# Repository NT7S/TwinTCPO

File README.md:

# Twin-T Code Practice Oscillator (Amogus Edition)

A battery-powered code practice oscillator for amateur radio operators. The
board is a two-layer, through-hole design built around a twin-T audio
oscillator feeding a pair of NE5532 buffers. The "Amogus" edition is a
novelty layout shaped and silkscreened as a crewmate.

## Overview

The oscillator core is a discrete common-emitter stage (Q2, 2N4401) with a
twin-T notch network in its feedback path. A MOSFET (Q1) buffers the key
input and drives a second MOSFET (Q3) that modulates the notch, giving a
clean keying envelope with a minimum of clicks. Two LEDs provide power and
key-down indication. The audio output is buffered by both halves of an
NE5532 and fed to a 1/8" headphone jack.

## Specifications

| Parameter | Value |
|-----------|-------|
| Supply | 9 V battery (6F22 / PP3) |
| Supply current | ~2 mA quiescent |
| Oscillator frequency | ~480 Hz nominal (1/(2πRC), R = 3.3 kΩ, C = 100 nF); verify by measurement |
| Output | 1/8" (3.5 mm) headphone jack, AC-coupled |
| Board size | 120.6 × 120.0 mm, 2-layer, 1.6 mm FR4 |
| Keying | MOSFET-switched twin-T notch; no audible clicks in normal use |

## Repository contents

| Path | Description |
|------|-------------|
| `pcb/` | KiCad project (schematic, board, Gerbers, drill) |
| `pcb/TwinTCPO.kicad_pcb` | KiCad board file (rev A as built, 2021) |
| `pcb/TwinTCPO.kicad_sch` | KiCad schematic (re-saved 2023, see rev notes) |
| `pcb/TwinTCPO*.gbr`, `pcb/TwinTCPO.drl` | Committed fabrication outputs (2021) |
| `BOM.csv` | Bill of materials, generated from the board's as-built values |
| `docs/REV-A-NOTES.md` | As-built revision notes and known discrepancies |
| `media/` | Artwork and mechanical assets (SVG, PDF, TIF, XCF) |

## Build notes

1. Use `BOM.csv` for parts; it reflects the **board as fabricated** (rev A,
   2021), not the current schematic. The `Notes` column flags every reference
   whose schematic value differs.
2. Read `docs/REV-A-NOTES.md` before ordering parts. In particular, **C11 is
   1 µF on the board but 100 µF in the schematic, and the schematic is the
   correct value** — at 32 Ω the as-built 1 µF rolls off from ~5 kHz and costs
   about 20 dB at the 480 Hz tone. Use 100 µF (or 47 µF) unless you specifically
   intend high-impedance headphones. **R6 is the opposite case: the board's
   3.3 kΩ is correct and the schematic's 330 Ω is the error.**
3. The committed Gerbers and drill file regenerate exactly from
   `TwinTCPO.kicad_pcb`; they are safe to send to a fabricator as-is.
4. The board has no mounting holes. Confirm your enclosure retains it.

## License

This design is licensed under the Creative Commons Attribution-ShareAlike 4.0
International License. See `LICENSE` for the full text. You are free to share
and adapt the design, provided you credit the original author and distribute
derivatives under the same terms.

## Links

- [Etherkit](https://www.etherkit.com)
- [NT7S / Jason Milldrum](https://nt7s.com)

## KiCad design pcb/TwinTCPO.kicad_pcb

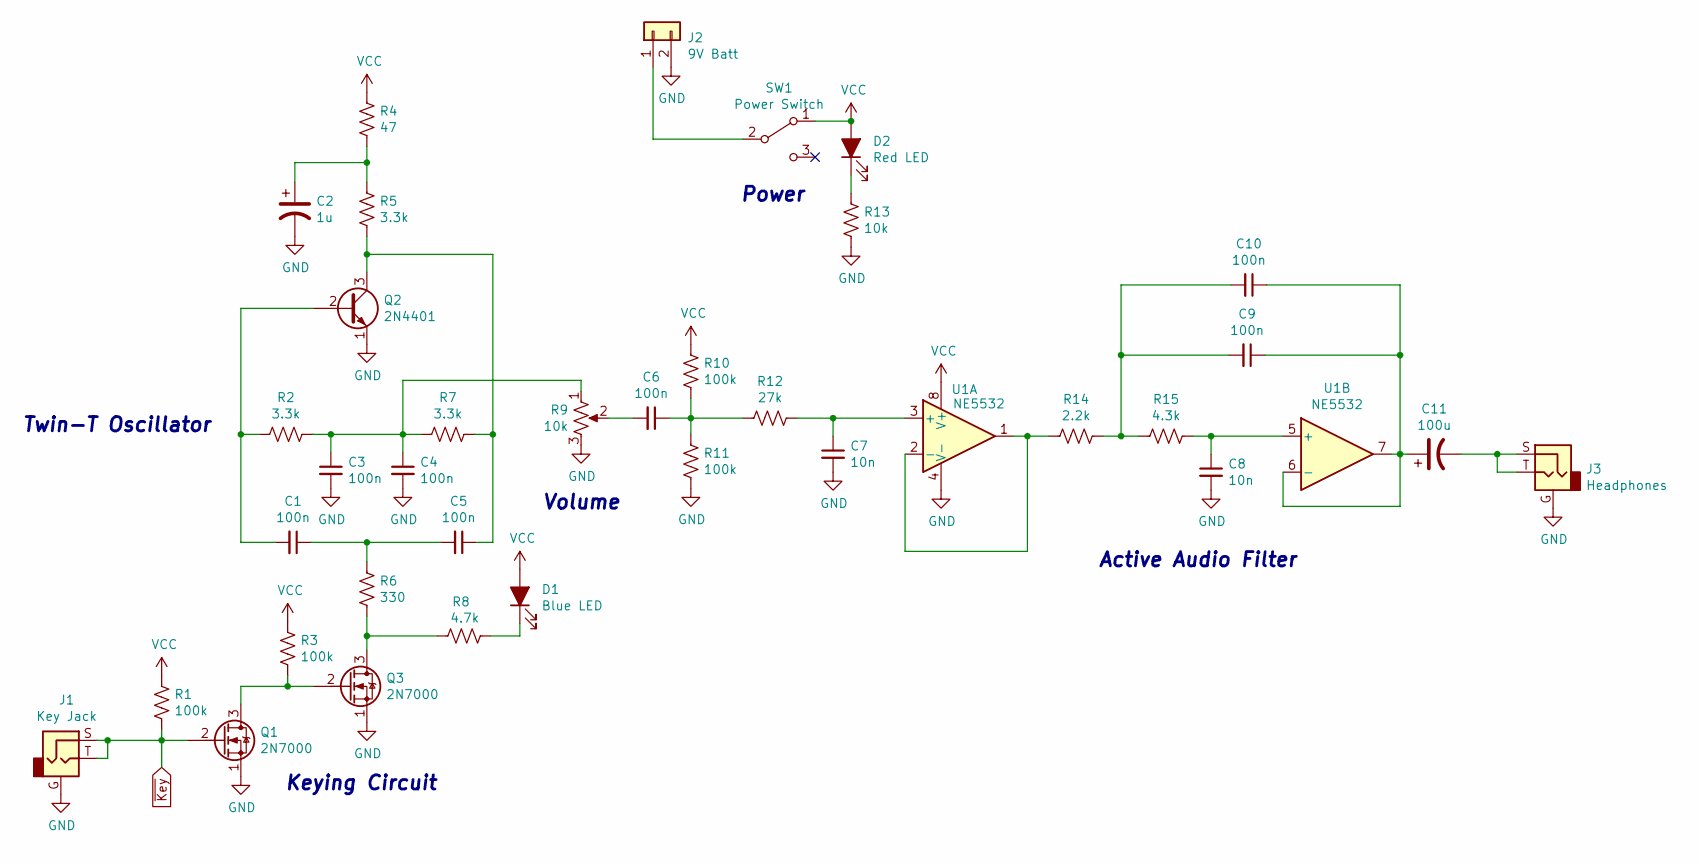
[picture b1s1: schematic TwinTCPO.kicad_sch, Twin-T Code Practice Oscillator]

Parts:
C1, C3, C4, C5, C6, C9, C10: 100n; C_Disc_D4.3mm_W1.9mm_P5.00mm
C2: 1u; CP_Radial_D5.0mm_P2.00mm
C7, C8: 10n; C_Disc_D4.3mm_W1.9mm_P5.00mm
C11: 100u; CP_Radial_D5.0mm_P2.00mm
D1: Blue LED; Kingbright_AA3528QBS_D09
D2: Red LED; LED_D5.0mm
J1: Key Jack; Kycon_STX-3120-3B
J2: 9V Batt; Eagle_12BH611-GR
J3: Headphones; Kycon_STX-3120-3B
Q1, Q3: 2N7000; TO-92_Inline
Q2: 2N4401; TO-92_Inline
R1, R3, R10, R11: 100k; R_Axial_DIN0207_L6.3mm_D2.5mm_P7.62mm_Horizontal
R2, R5, R7: 3.3k; R_Axial_DIN0207_L6.3mm_D2.5mm_P7.62mm_Horizontal
R4: 47; R_Axial_DIN0207_L6.3mm_D2.5mm_P7.62mm_Horizontal
R6: 330; R_Axial_DIN0207_L6.3mm_D2.5mm_P7.62mm_Horizontal
R8: 4.7k; R_Axial_DIN0207_L6.3mm_D2.5mm_P7.62mm_Horizontal
R9: 10k; Piher_N6L25T3N-103-3030
R12: 27k; R_Axial_DIN0207_L6.3mm_D2.5mm_P7.62mm_Horizontal
R13: 10k; R_Axial_DIN0207_L6.3mm_D2.5mm_P7.62mm_Horizontal
R14: 2.2k; R_Axial_DIN0207_L6.3mm_D2.5mm_P7.62mm_Horizontal
R15: 4.3k; R_Axial_DIN0207_L6.3mm_D2.5mm_P7.62mm_Horizontal
SW1: Power Switch; C&K_OS102011MS2QN1
U1: NE5532; DIP-8_W7.62mm_LongPads

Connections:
GND: C2.2, C3.2, C4.2, C7.2, C8.2, J1.G, J2.2, J3.G, Q1.1 (S), Q2.1 (E), Q3.1 (S), R9.3, R11.2, R13.2, U1.4 (V-)
unnamed: C1.1, C5.2, R6.1
unnamed: C1.2, Q2.2 (B), R2.1
unnamed: C2.1, R4.2, R5.1
unnamed: C3.1, C4.1, R2.2, R7.1, R9.1
unnamed: C5.1, Q2.3 (C), R5.2, R7.2
unnamed: C6.1, R10.2, R11.1, R12.1
unnamed: C6.2, R9.2
unnamed: C7.1, R12.2, U1.3 (+)
unnamed: C8.1, R15.2, U1.5 (+)
unnamed: C9.1, C10.1, C11.1, U1.6 (-), U1.7
unnamed: C9.2, C10.2, R14.2, R15.1
unnamed: C11.2, J3.S, J3.T
unnamed: D1.1 (K), R8.1
unnamed: D2.1 (K), R13.1
unnamed: J2.1, SW1.2 (B)
unnamed: Q1.3 (D), Q3.2 (G), R3.2
unnamed: Q3.3 (D), R6.2, R8.2
unnamed: R14.1, U1.1, U1.2 (-)
VCC: D1.2 (A), D2.2 (A), R1.1, R3.1, R4.1, R10.1, SW1.1 (A), U1.8 (V+)
~Key: J1.S, J1.T, Q1.2 (G), R1.2

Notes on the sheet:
Power
Keying Circuit
Volume
Active Audio Filter
Twin-T Oscillator

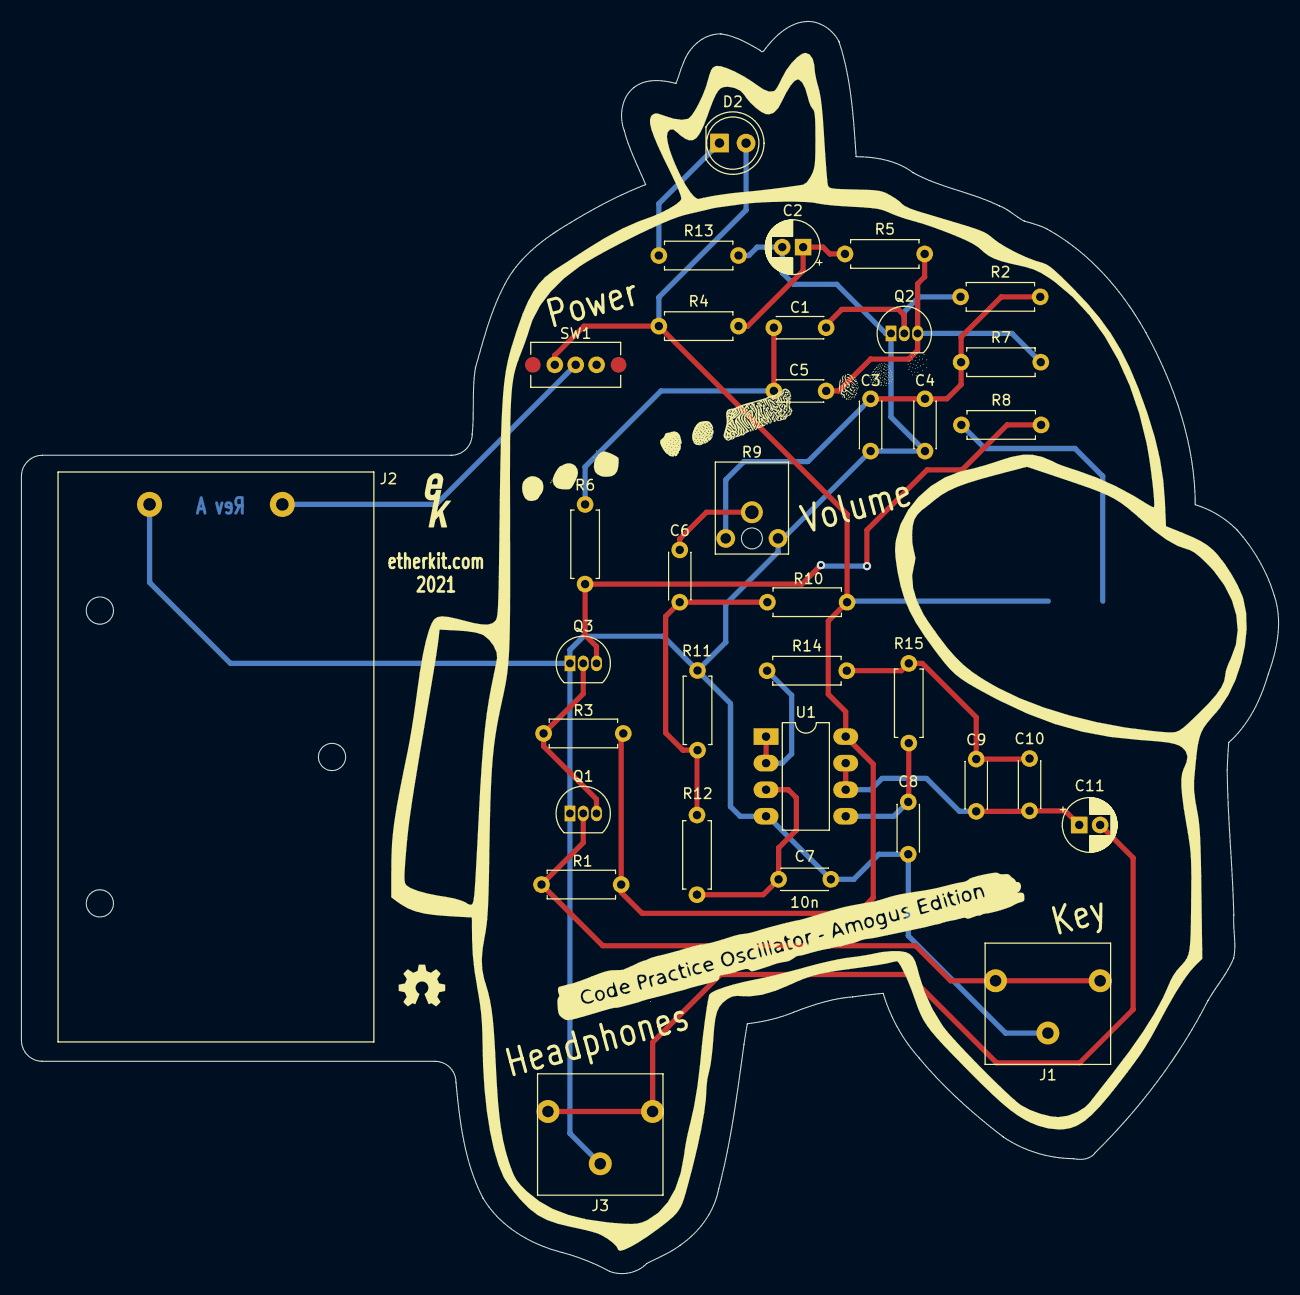
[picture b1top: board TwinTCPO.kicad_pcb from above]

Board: 2 copper layers, 120.2 x 119.7 mm, 37 parts (1 on the bottom side), 21 nets.

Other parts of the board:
Ref**: Val**; EtherkitLogoSmall

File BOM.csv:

Quantity,Reference(s),Value,Footprint,Notes
7,C1 C3 C4 C5 C6 C9 C10,100n,Capacitor_THT:C_Disc_D4.3mm_W1.9mm_P5.00mm,
2,C2 C11,1u,Capacitor_THT:CP_Radial_D5.0mm_P2.00mm,Schematic shows C11=100u
2,C7 C8,10n,Capacitor_THT:C_Disc_D4.3mm_W1.9mm_P5.00mm,
1,D1,Blue LED,EtherkitKicadLibrary:Kingbright_AA3528QBS_D09,
1,D2,Red LED,LED_THT:LED_D5.0mm,
1,J1,Key Jack,EtherkitKicadLibrary:Kycon_STX-3120-3B,
1,J2,9V Batt,EtherkitKicadLibrary:Eagle_12BH611-GR,
1,J3,Headphones,EtherkitKicadLibrary:Kycon_STX-3120-3B,
2,Q1 Q3,2N7000,Package_TO_SOT_THT:TO-92_Inline,
1,Q2,2N4401,Package_TO_SOT_THT:TO-92_Inline,
2,R1 R3,10k,Resistor_THT:R_Axial_DIN0207_L6.3mm_D2.5mm_P7.62mm_Horizontal,"Schematic shows R1=100k, R3=100k"
4,R2 R5 R6 R7,3.3k,Resistor_THT:R_Axial_DIN0207_L6.3mm_D2.5mm_P7.62mm_Horizontal,Schematic shows R6=330
1,R4,47,Resistor_THT:R_Axial_DIN0207_L6.3mm_D2.5mm_P7.62mm_Horizontal,
2,R8 R13,4.7k,Resistor_THT:R_Axial_DIN0207_L6.3mm_D2.5mm_P7.62mm_Horizontal,Schematic shows R13=10k
1,R9,10k,EtherkitKicadLibrary:Piher_N6L25T3N-103-3030,
2,R10 R11,100k,Resistor_THT:R_Axial_DIN0207_L6.3mm_D2.5mm_P7.62mm_Horizontal,
1,R12,27k,Resistor_THT:R_Axial_DIN0207_L6.3mm_D2.5mm_P7.62mm_Horizontal,
1,R14,2.2k,Resistor_THT:R_Axial_DIN0207_L6.3mm_D2.5mm_P7.62mm_Horizontal,
1,R15,4.3k,Resistor_THT:R_Axial_DIN0207_L6.3mm_D2.5mm_P7.62mm_Horizontal,
1,SW1,Power Switch,EtherkitKicadLibrary:C&K_OS102011MS2QN1,
1,U1,NE5532,Package_DIP:DIP-8_W7.62mm_LongPads,

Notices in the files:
pcb/TwinTCPO.kicad_pcb:
Creative Commons 4.0
CC-BY-SA
pcb/TwinTCPO.kicad_sch:
Creative Commons 4.0 CC-BY-SA
